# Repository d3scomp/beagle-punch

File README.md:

# beagle-punch
Punch press simulator on BeagleBone Black.

The simulator consists of three elements:
1) Simulator on BBB - simulates a punch press at realtime
2) PC visualizer - connects to simulator on BBB via UART and displays the position of the punch press head and punches made
3) Skeleton of a controller for STM32F4 Discovery - connects to simulator on BBB via SPI and controls the operation of the punch press

Setup instructions can be found in instructions.txt

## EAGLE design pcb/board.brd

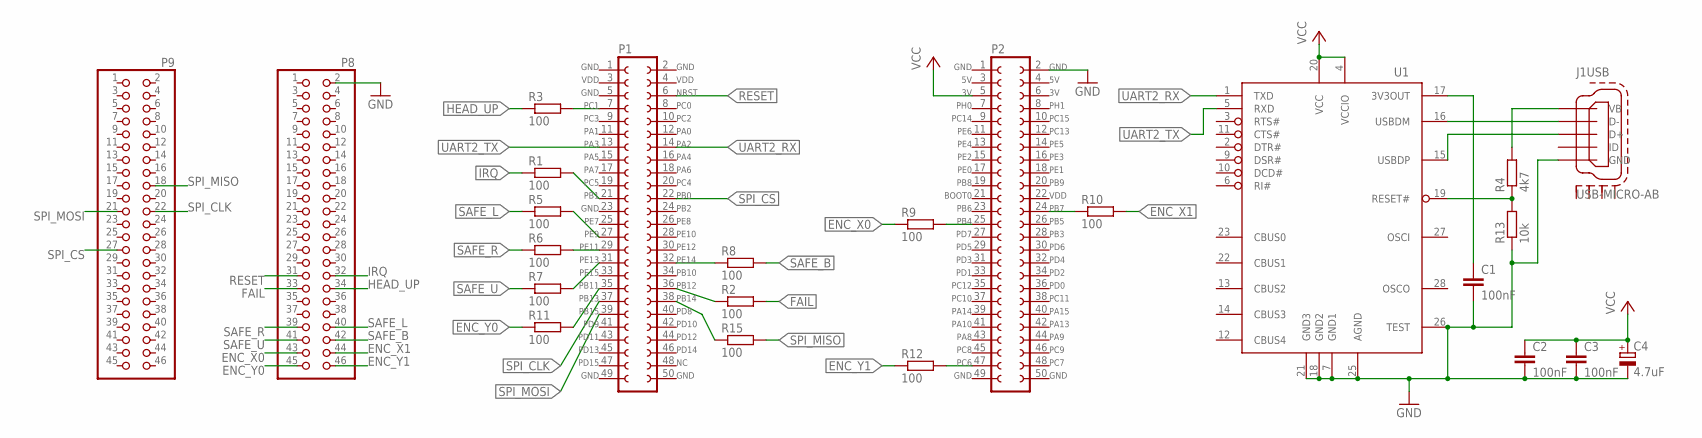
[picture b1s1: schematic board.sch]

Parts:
C1, C2, C3: 100nF; C025-024X044
C4: 4.7uF; E15-5
J1: USB-MICRO-AB
P1: PIN-F-2X25-DISC-P1; PIN-F-2X25
P2: PIN-F-2X25-DISC-P2; PIN-F-2X25
P8, P9: PIN-M-2X23
R1, R2, R3, R5, R6, R7, R8, R9, R10, R11, R12, R15: 100; 0204/5
R4: 4k7; 0204/5
R13: 10k; 0204/5
U1: FT232RL; SSOP28DB

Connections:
ENC_X0: P8.43, R9.1
ENC_X1: P8.44, R10.2
ENC_Y0: P8.45, R11.1
ENC_Y1: P8.46, R12.1
FAIL: P8.33, R2.2
GND: C1.2, C2.2, C3.2, C4.-, J1.P$5 (GND), P2.2, P8.2, R13.1, U1.7 (GND1), U1.18 (GND2), U1.21 (GND3), U1.25 (AGND), U1.26 (TEST)
HEAD_UP: P8.34, R3.1
IRQ: P8.32, R1.1
unnamed: P1.21, R1.2
unnamed: J1.P$2 (D-), U1.16 (USBDM)
unnamed: P1.38, R15.1
unnamed: C1.1, U1.17 (3V3OUT)
unnamed: P1.36, R2.1
unnamed: J1.P$3 (D+), U1.15 (USBDP)
unnamed: J1.P$1 (VB), R4.2
unnamed: R4.1, R13.2, U1.19 (RESET#)
unnamed: P1.7, R3.2
unnamed: P1.27, R5.2
unnamed: P1.29, R6.2
unnamed: P1.31, R7.2
unnamed: P1.32, R8.1
unnamed: P1.35, R11.2
unnamed: P2.25, R9.2
unnamed: P2.24, R10.1
unnamed: P2.47, R12.2
RESET: P1.6, P8.31
SAFE_B: P8.42, R8.2
SAFE_L: P8.40, R5.1
SAFE_R: P8.39, R6.1
SAFE_U: P8.41, R7.1
SPI_CLK: P1.37, P9.22
SPI_CS: P1.22, P9.27
SPI_MISO: P9.18, R15.2
SPI_MOSI: P1.39, P9.21
UART2_RX: P1.14, U1.1 (TXD)
UART2_TX: P1.13, U1.5 (RXD)
VCC: C2.1, C3.1, C4.+, P2.5, U1.4 (VCCIO), U1.20 (VCC)

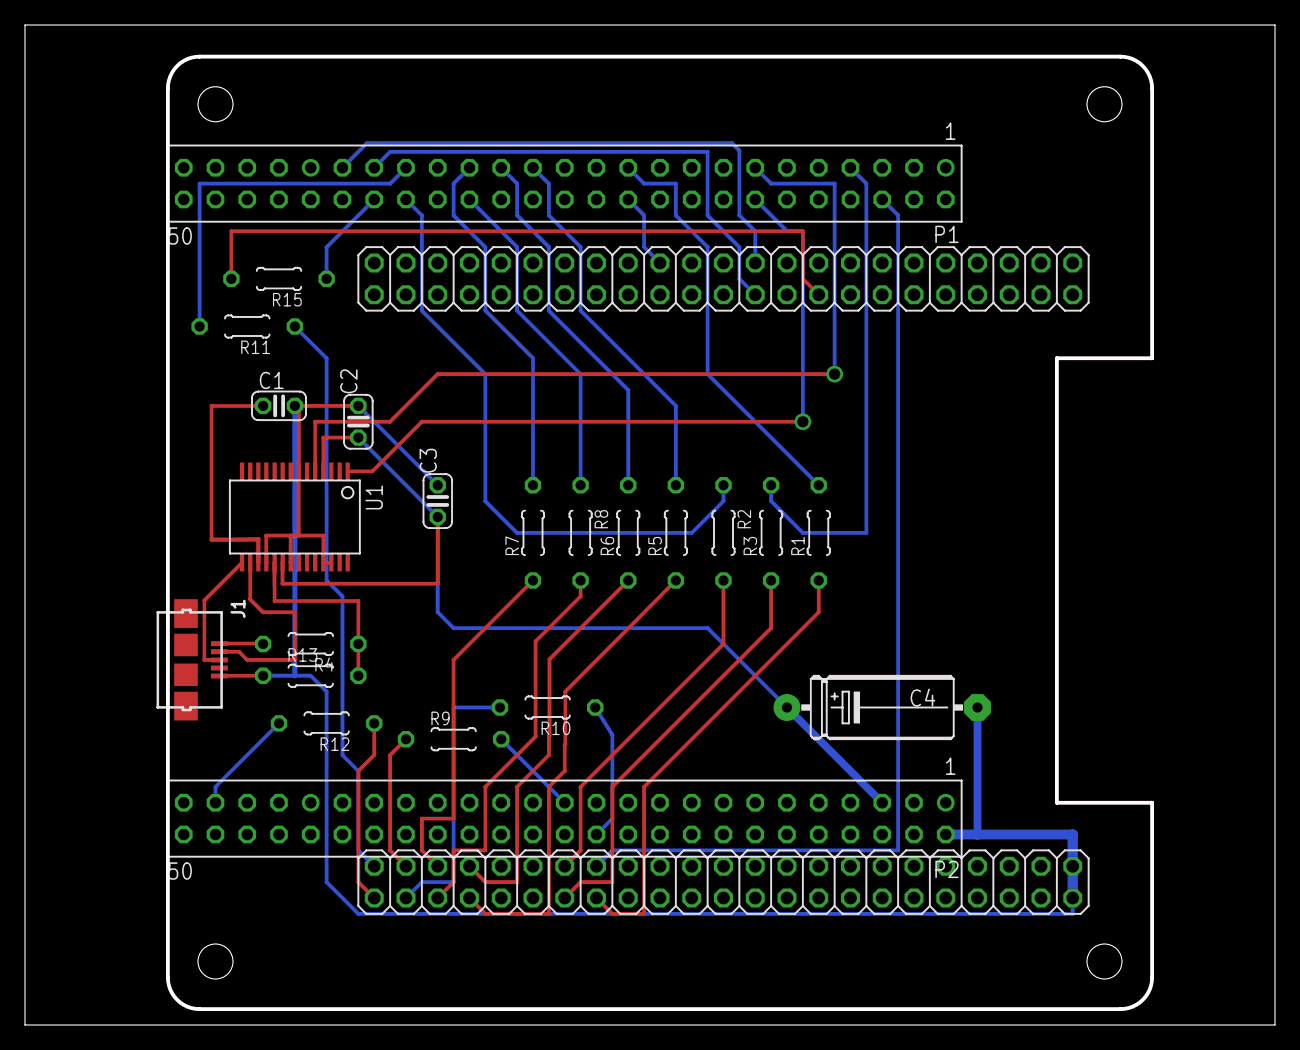
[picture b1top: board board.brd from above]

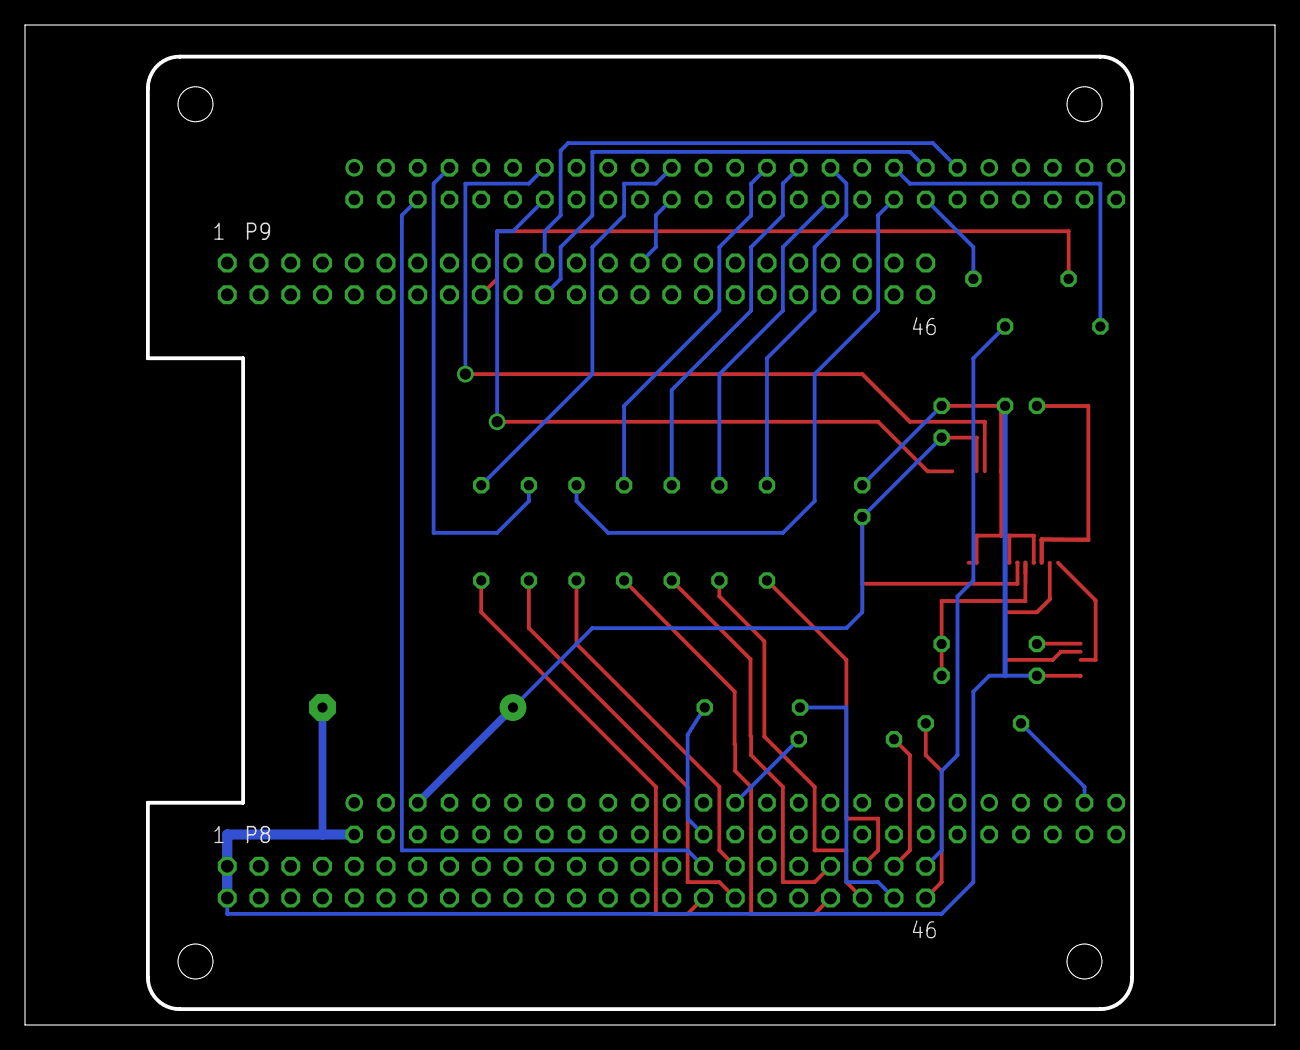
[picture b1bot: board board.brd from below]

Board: 2 copper layers, 99.7 x 79.7 mm, 24 parts (2 on the bottom side), 37 nets.

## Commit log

2015-12-08 Gitignore
2015-12-08 Plant files
2015-12-08 Fix - wrong license (modules could not find exported GPL symbols)
2015-12-08 Fixes
2015-12-08 License added
2015-12-08 Updated instructions
2015-12-08 README.md created
2015-12-08 Initial commit of the visualizer
2015-12-22 FreeRTOS stub
2015-12-22 Updates in punch-eval
2015-12-22 Compiles
2015-12-23 Seems to communicate
2015-12-23 Main2 removed
2016-01-25 Refactoring / cleanup - does not compile
2016-01-25 Modules compile
2016-01-25 Renaming
2016-02-01 Building dist
2016-02-01 Deleted some old files
2016-02-01 Updated default path to toolchain
2016-02-03 Updates in sim.
    Commands changed to comply with the original assignment.
    Added 9 more PINs for direct reporting of the state.
2016-02-06 Experiments with pin assignment
2016-02-06 Pin reassignment
2016-02-09 Updated pin assignment
2016-02-09 Eagle schema - draft
2016-02-09 Pin layout
2016-02-09 Small improvement
2016-02-10 Switch of SAFE_L and SAFE_R pins to make routing on the board easier
